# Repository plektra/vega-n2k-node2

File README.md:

# vega-n2k-node2
NMEA 2000 sensor node 2

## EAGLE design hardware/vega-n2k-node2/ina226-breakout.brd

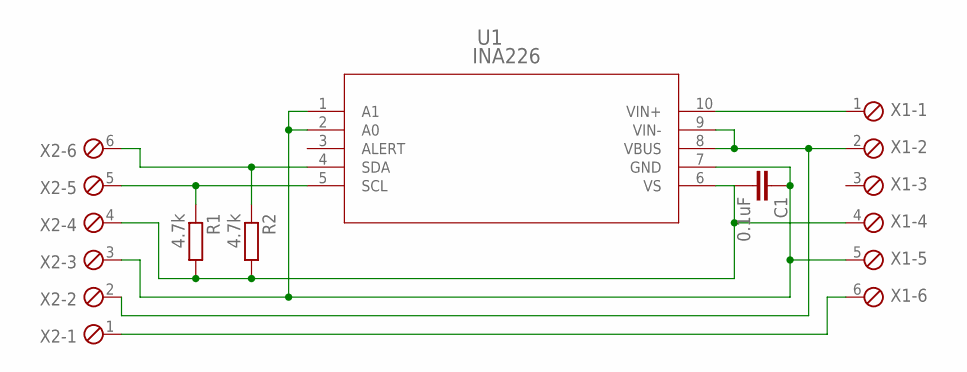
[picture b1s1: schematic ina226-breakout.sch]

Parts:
C1: 0.1uF; C0603
R1, R2: 4.7k; R0603
U1: INA226; DGS10; MANUFACTURER_PART_NUMBER INA226
X1, X2: MPT6; 6POL254

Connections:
1-WIRE: X1.6, X2.1
GND: C1.1, U1.1 (A1), U1.2 (A0), U1.7 (GND), X1.5, X2.3
SCL: R1.1, U1.5 (SCL), X2.5
SDA: R2.1, U1.4 (SDA), X2.6
VIN+: U1.10 (VIN+), X1.1
VIN-: U1.8 (VBUS), U1.9 (VIN-), X1.2, X2.2
VS: C1.2, R1.2, R2.2, U1.6 (VS), X1.4, X2.4

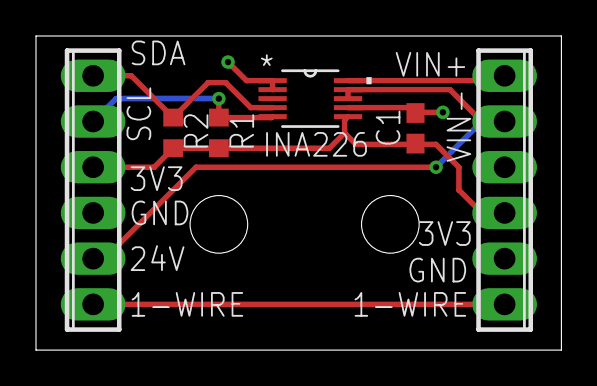
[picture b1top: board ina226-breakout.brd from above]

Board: 2 copper layers, 29.2 x 17.4 mm, 6 parts (0 on the bottom side), 7 nets.

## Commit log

2022-05-09 first working version for battery monitoring
2022-05-09 ignore .vscode
2022-05-09 github workflow for uploading firmware to S3
2024-10-23 update packages, add logging

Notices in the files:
parts and their libraries:
COPYRIGHT: Copyright (C) 2022 Ultra Librarian. All rights reserved.
